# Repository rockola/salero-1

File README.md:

# salero-1
Salero-1 PCB, clone of LPB-1 buffer

* v0.1: initial import, complete, verified

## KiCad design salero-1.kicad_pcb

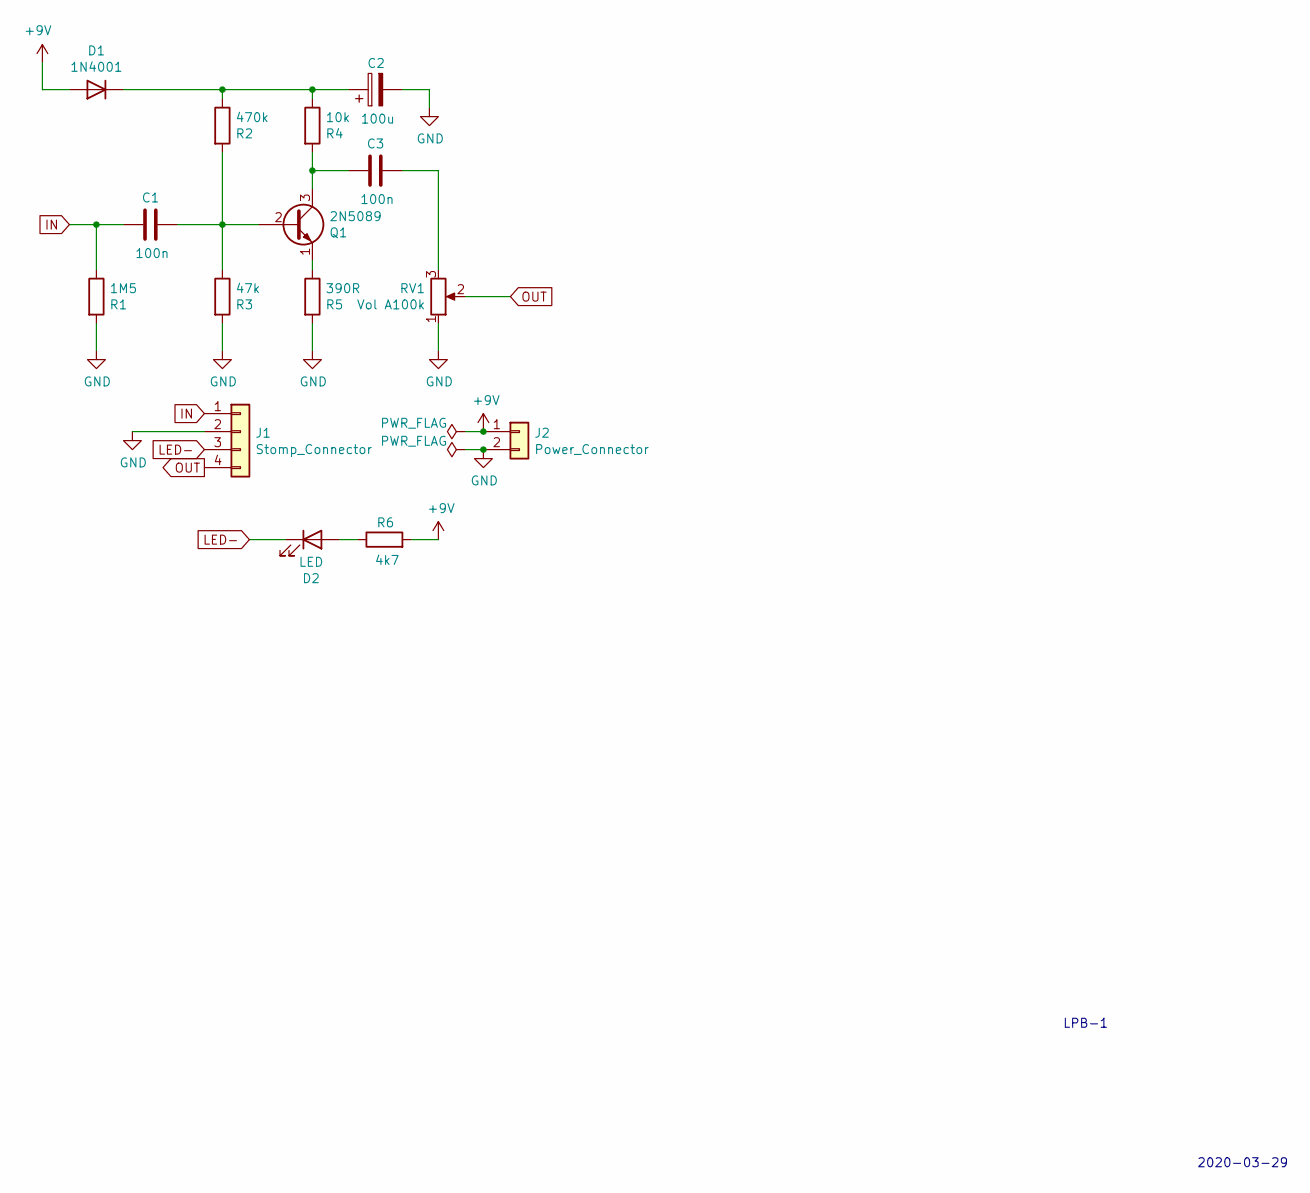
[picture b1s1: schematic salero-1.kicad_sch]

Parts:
C1, C3: 100n; C_Box_7.2_2.5
C2: 100u; CP_Radial_D6.3mm_P2.50mm
D1: 1N4001; D_DO-41_SOD81_P10.16mm_Horizontal
D2: LED; LED_D3.0mm
J1: Stomp_Connector; Stomp_4pin
J2: Power_Connector; Power_Header_2pin_TOP
Q1: 2N5089; TO92_EBC
R1: 1M5; R_DIN0207
R2: 470k; R_DIN0207
R3: 47k; R_DIN0207
R4: 10k; R_DIN0207
R5: 390R; R_DIN0207
R6: 4k7; R_DIN0207
RV1: Vol A100k; 16mm_BoardMount

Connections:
+9V: D1.2 (A), J2.1 (PWR), R6.2
GND: C2.2, J1.2 (GND), J2.2 (GND), R1.2, R3.2, R5.2, RV1.1
IN: C1.1, J1.1 (IN), R1.1
LED-: D2.1 (K), J1.3 (SW)
unnamed: C1.2, Q1.2 (B), R2.2, R3.1
unnamed: C2.1, D1.1 (K), R2.1, R4.1
unnamed: C3.1, Q1.3 (C), R4.2
unnamed: C3.2, RV1.3
unnamed: D2.2 (A), R6.1
unnamed: Q1.1 (E), R5.1
OUT: J1.4 (OUT), RV1.2

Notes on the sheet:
2020-03-29
LPB-1

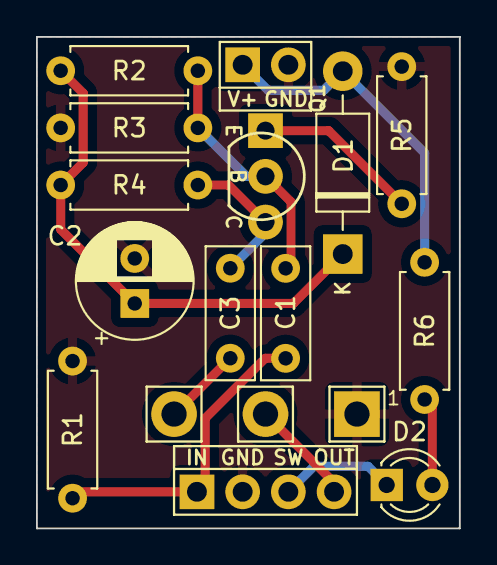
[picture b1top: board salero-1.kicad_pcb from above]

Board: 2 copper layers, 23.5 x 27.3 mm, 15 parts (0 on the bottom side), 11 nets.

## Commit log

2020-03-29 v0.1: initial
2020-03-29 v0.1: images from jlcpcb gerber viewer
2020-03-29 oshpark preview
2020-05-21 Verification build OK
    v0.1 PCB has been built & verified to work OK
2022-01-11 ignore backups directory
2022-01-11 updated to KiCad 6.0
2022-04-14 Salero-1 schematic image
2022-04-14 Add schematic image
